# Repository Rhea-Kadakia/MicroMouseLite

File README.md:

# Jerry - the hand warden gesture bot 3000
# A PID controlled, gesture recognizing autonomous robot

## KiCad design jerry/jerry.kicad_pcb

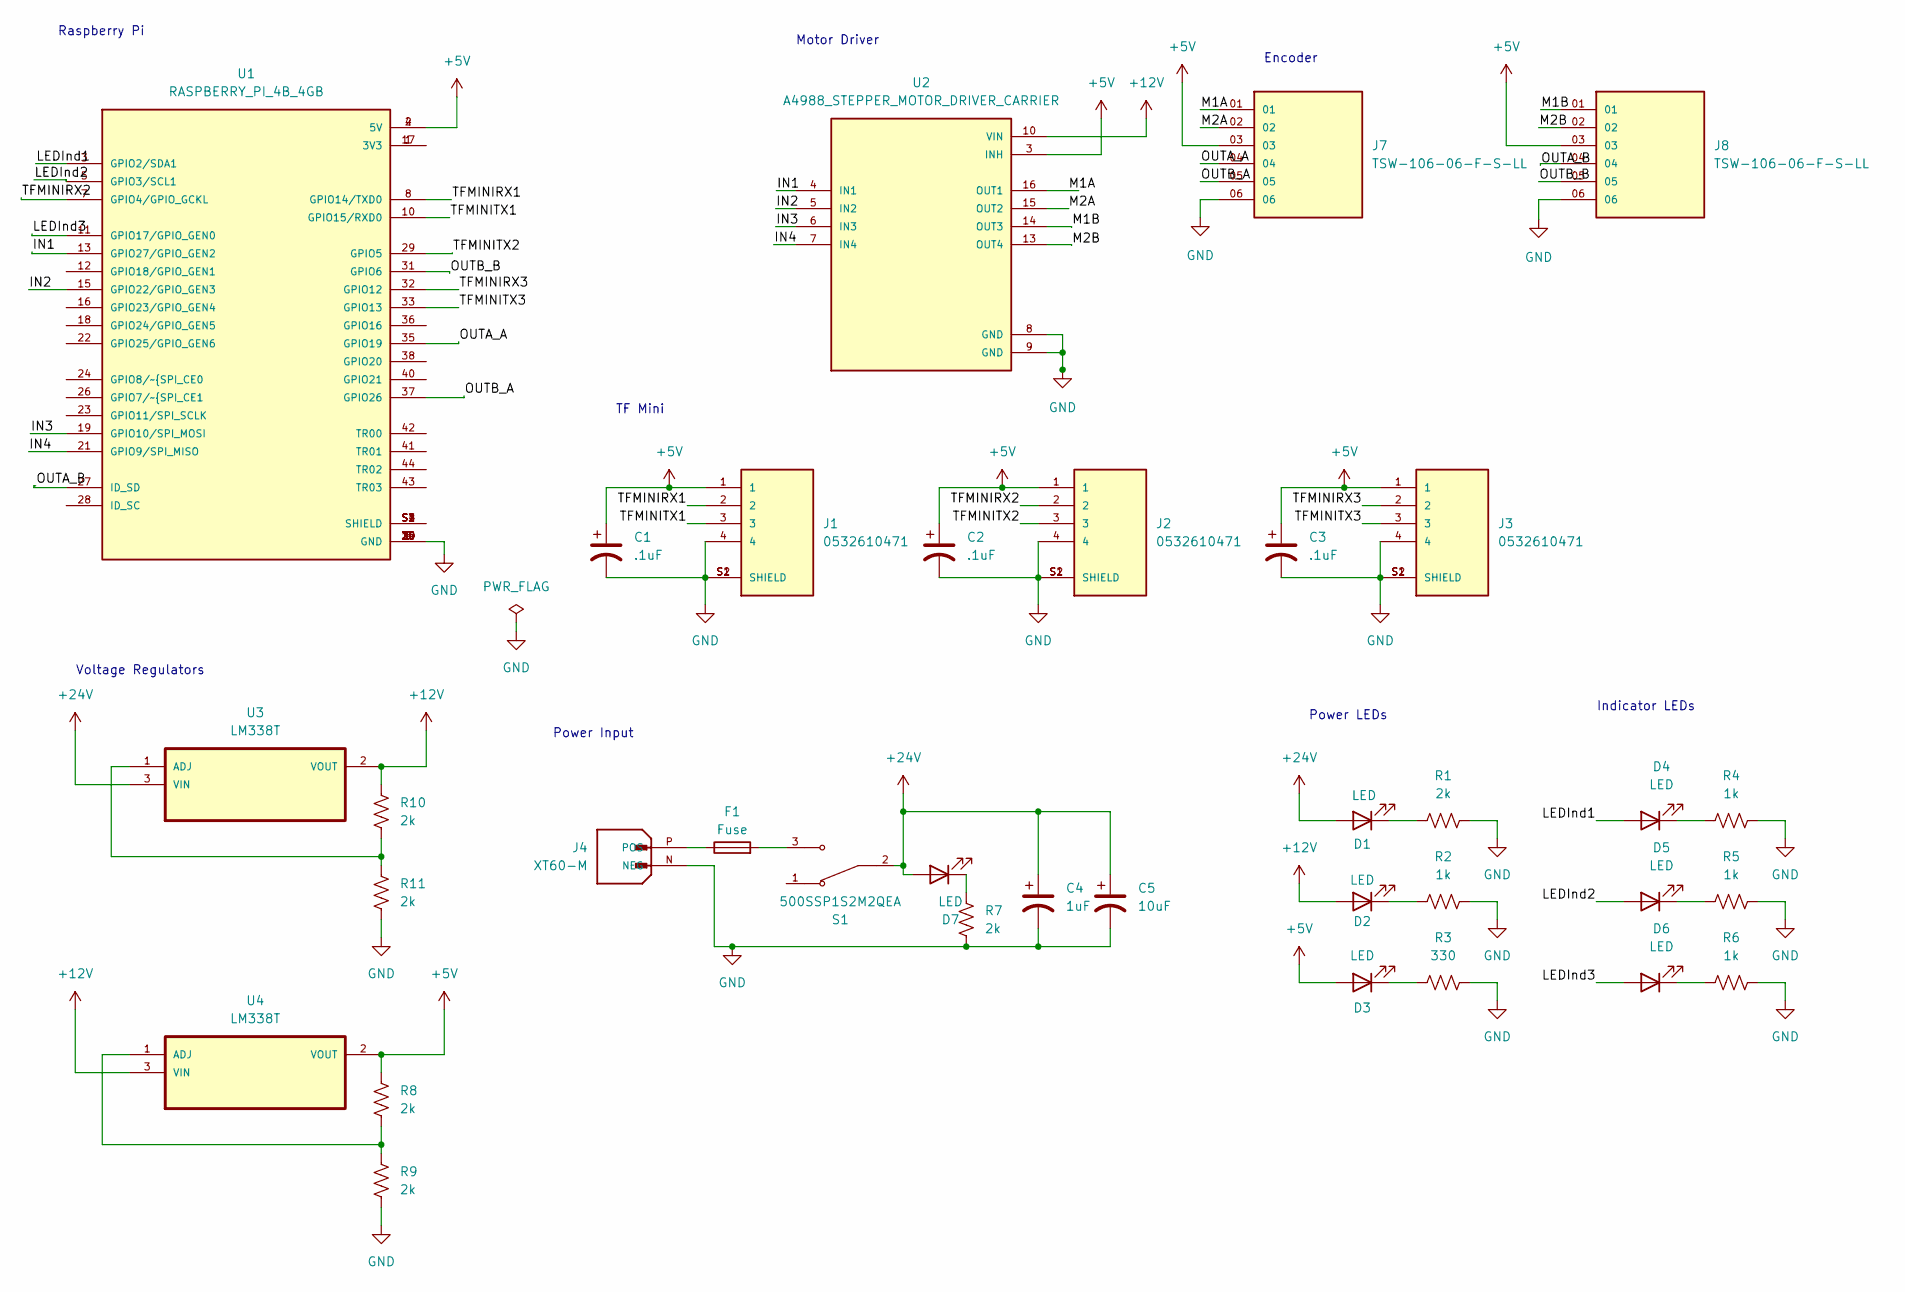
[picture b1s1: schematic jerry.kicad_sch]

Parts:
C1, C2, C3: .1uF; C_0201_0603Metric_Pad0.64x0.40mm_HandSolder
C4: 1uF; C_0201_0603Metric_Pad0.64x0.40mm_HandSolder
C5: 10uF; C_0201_0603Metric_Pad0.64x0.40mm_HandSolder
D1, D2, D3, D4, D5, D6, D7: LED; D_0201_0603Metric_Pad0.64x0.40mm_HandSolder
F1: Fuse; FUSC3215X83N
J1, J2, J3: 0532610471; MOLEX_0532610471
J4: XT60-M; AMASS_XT60-M
J7, J8: TSW-106-06-F-S-LL; SAMTEC_TSW-106-06-F-S-LL
R1, R7, R8, R9, R10, R11: 2k; R_0201_0603Metric_Pad0.64x0.40mm_HandSolder
R2, R4, R5, R6: 1k; R_0201_0603Metric_Pad0.64x0.40mm_HandSolder
R3: 330; R_0201_0603Metric_Pad0.64x0.40mm_HandSolder
S1: 500SSP1S2M2QEA; SW_500SSP1S2M2QEA; PARTREV C
U1: RASPBERRY_PI_4B_4GB; MODULE_RASPBERRY_PI_4B_4GB
U2: A4988_STEPPER_MOTOR_DRIVER_CARRIER; MODULE_A4988_STEPPER_MOTOR_DRIVER_CARRIER
U3, U4: LM338T; TO254P1054X470X1955-3

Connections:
+5V: C1.1, C2.1, C3.1, D3.2 (A), J1.1, J2.1, J3.1, J7.03, J8.03, R8.2, U1.2 (5V), U1.4 (5V), U2.3 (INH), U4.2 (VOUT)
+12V: D2.2 (A), R10.2, U2.10 (VIN), U3.2 (VOUT), U4.3 (VIN)
+24V: C4.1, C5.1, D1.2 (A), D7.2 (A), S1.2, U3.3 (VIN)
/IN1: U1.13 (GPIO27/GPIO_GEN2), U2.4 (IN1)
/IN2: U1.15 (GPIO22/GPIO_GEN3), U2.5 (IN2)
/IN3: U1.19 (GPIO10/SPI_MOSI), U2.6 (IN3)
/IN4: U1.21 (GPIO9/SPI_MISO), U2.7 (IN4)
/LEDInd1: D4.2 (A), U1.3 (GPIO2/SDA1)
/LEDInd2: D5.2 (A), U1.5 (GPIO3/SCL1)
/LEDInd3: D6.2 (A), U1.11 (GPIO17/GPIO_GEN0)
/M1A: J7.01, U2.16 (OUT1)
/M1B: J8.01, U2.14 (OUT3)
/M2A: J7.02, U2.15 (OUT2)
/M2B: J8.02, U2.13 (OUT4)
/OUTA_A: J7.04, U1.35 (GPIO19)
/OUTA_B: J8.04, U1.27 (ID_SD)
/OUTB_A: J7.05, U1.37 (GPIO26)
/OUTB_B: J8.05, U1.31 (GPIO6)
/TFMINIRX1: J1.2, U1.8 (GPIO14/TXD0)
/TFMINIRX2: J2.2, U1.7 (GPIO4/GPIO_GCKL)
/TFMINIRX3: J3.2, U1.32 (GPIO12)
/TFMINITX1: J1.3, U1.10 (GPIO15/RXD0)
/TFMINITX2: J2.3, U1.29 (GPIO5)
/TFMINITX3: J3.3, U1.33 (GPIO13)
GND: C1.2, C2.2, C3.2, C4.2, C5.2, J1.4, J1.S1 (SHIELD), J1.S2 (SHIELD), J2.4, J2.S1 (SHIELD), J2.S2 (SHIELD), J3.4, J3.S1 (SHIELD), J3.S2 (SHIELD), J4.N (NEG), J7.06, J8.06, R1.2, R2.2, R3.2, R4.2, R5.2, R6.2, R7.1, R9.1, R11.1, U1.6 (GND), U1.9 (GND), U1.14 (GND), U1.20 (GND), U1.25 (GND), U1.30 (GND), U1.34 (GND), U1.39 (GND), U2.8 (GND), U2.9 (GND)
unnamed: D1.1 (K), R1.1
unnamed: D2.1 (K), R2.1
unnamed: D3.1 (K), R3.1
unnamed: D4.1 (K), R4.1
unnamed: D5.1 (K), R5.1
unnamed: D6.1 (K), R6.1
unnamed: D7.1 (K), R7.2
unnamed: F1.2, S1.3
unnamed: F1.1, J4.P (POS)
unnamed: U1.1 (3V3), U1.17 (3V3)
unnamed: U1.S1 (SHIELD), U1.S2 (SHIELD), U1.S3 (SHIELD), U1.S4 (SHIELD)
unnamed: R10.1, R11.2, U3.1 (ADJ)
unnamed: R8.1, R9.2, U4.1 (ADJ)

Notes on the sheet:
Voltage Regulators
Power Input
Motor Driver
Indicator LEDs
Power LEDs
TF Mini
Encoder
Raspberry Pi

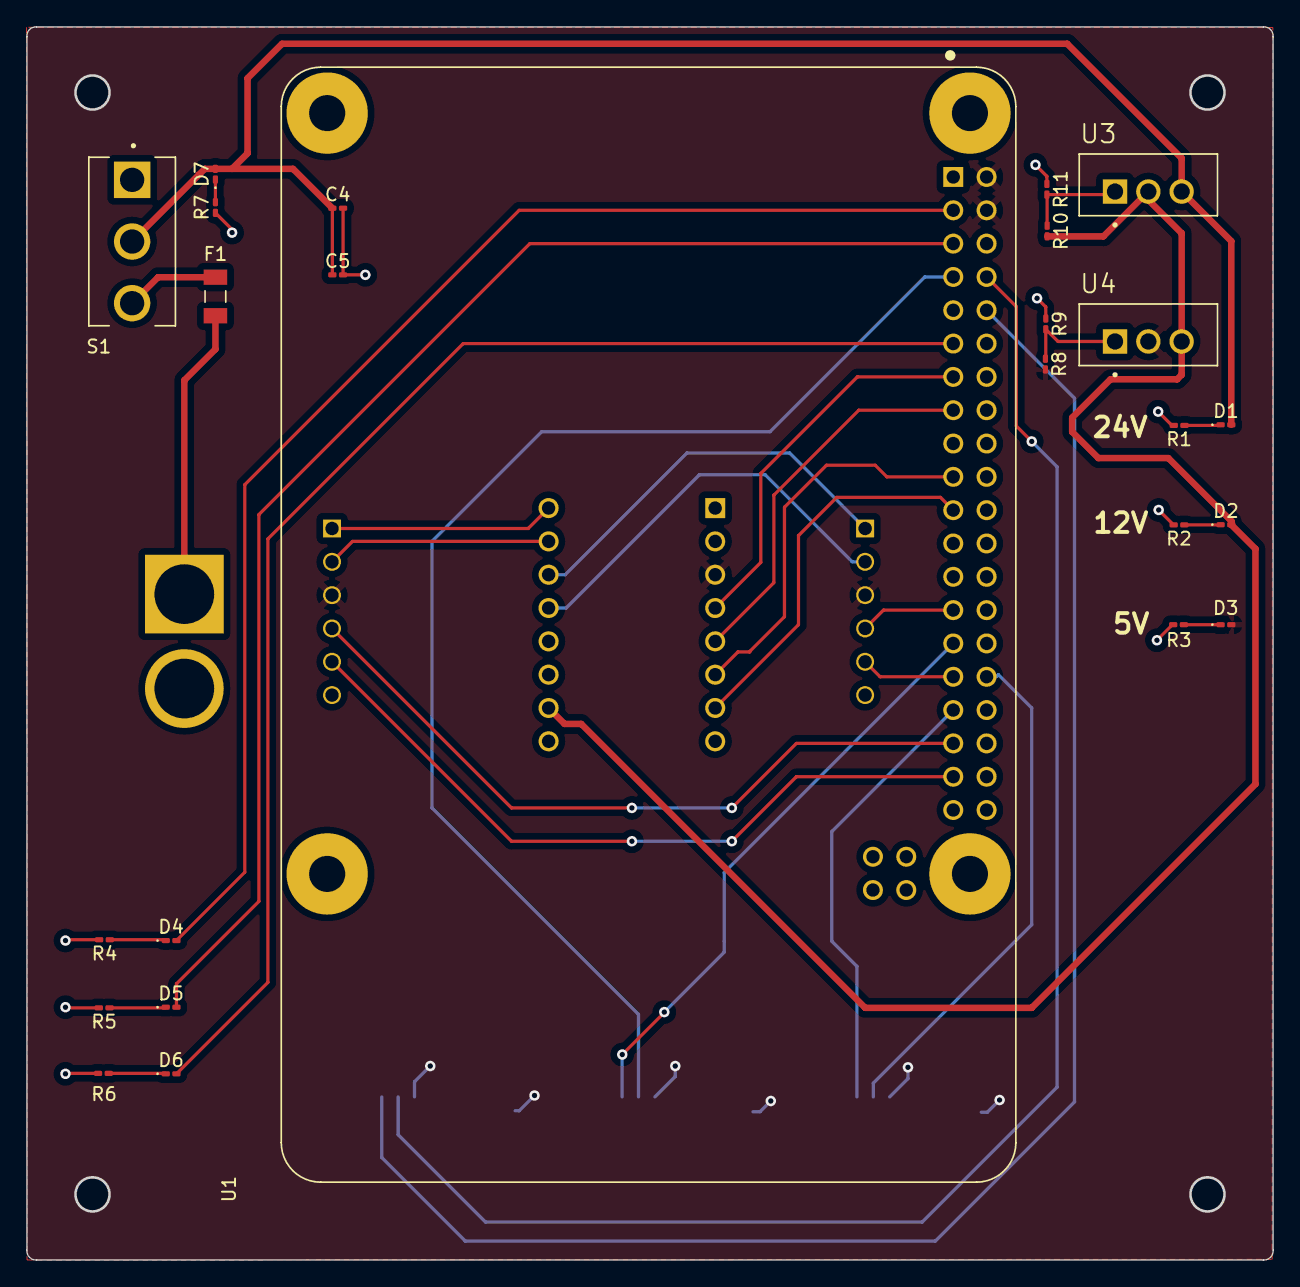
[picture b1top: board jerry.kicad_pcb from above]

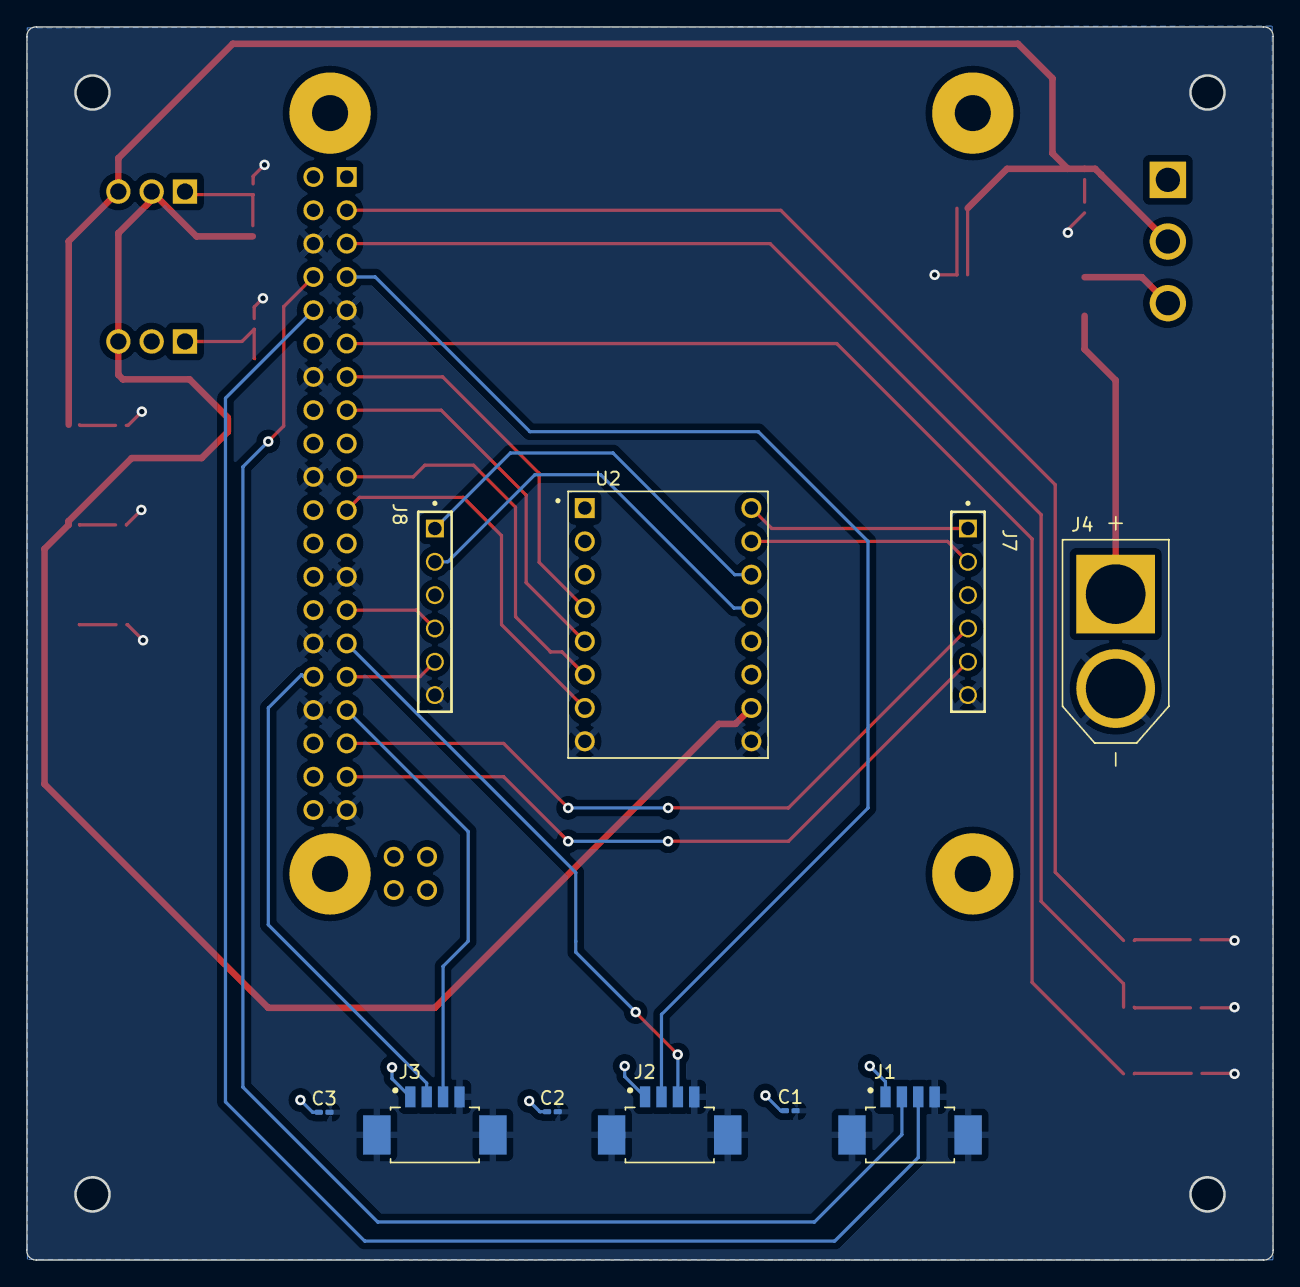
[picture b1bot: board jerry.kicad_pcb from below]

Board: 2 copper layers, 95.0 x 94.0 mm, 35 parts (10 on the bottom side), 38 nets.

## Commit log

2023-06-29 initial commit
    created kicad schematic
2023-07-19 Added Rasberry Pi, LED symbols
2023-07-21 Imported Parts
2023-07-28 some updates
    updated schematic, added components
2023-08-02 Voltage regulators. encoders
2023-08-02 Encoder Schematic
2023-08-09 Finished PCB
2023-08-12 Updated for manufacturing
    fixed gerber errors, genereated gerbers
